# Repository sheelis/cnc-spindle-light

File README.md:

# Circular LED strip PCB for CNC spindle light

This is a PCB and spindle attachment design and software to light up the CNC work area from all sides in any color or sequence desired (as long as you can program it to). The LED control is done by FastLED library, so it's not too hard to create your own sequences.

There is also an option to insert 2 lasers at 90* difference from each other in order to produce a cross shape on XY plane exactly where the tool will touch the work piece. Lasers have their own connectors and on/off switch on the PCB.
There is also a provision for attaching the the Z probe to the pcb, but it is only tested on my own DIY CNC.

You will find here:
- Firmware for ATTiny85
- PCB design
- Spindle mount design

## Final result

Then milled the wooden mount and attached the LED ring and lasers. I did not insert the lasers fully because later i will need to rotate them to align with center.

The mounting holes on the PCB align with any 20mm increment profiles such as my 2080 C-beam

PCB milled with a 0.2mm HSS bit

And the assembled PCB

## Parts list

This project requires:
- 1x WS2812B LED strip (circular, 24 LEDs)
- 1x ATTiny85
- 2x line or cross lasers
- 1x button and 1x switch
- some 2.54mm headers and sockets
- 2x THT resistors (10K)
- 1x single-sided copper board
- wooden block for milling the mount from
- 1x arduino uno (only for programming the ATTiny85)

## Usage

1. Mill or 3D print the mount.
2. Mill or etch the PCB at home or get it done by a PCB factory.
3. Upload the firmware to ATTiny85 using your preferred method. I used an arduino UNO as ISP.
4. Solder on all the components (I suggest starting with the smallest ones)
5. Connect the 5v power and LED strip to PCB
6. Press the button to change the LED mode

PM me for questions and comments!

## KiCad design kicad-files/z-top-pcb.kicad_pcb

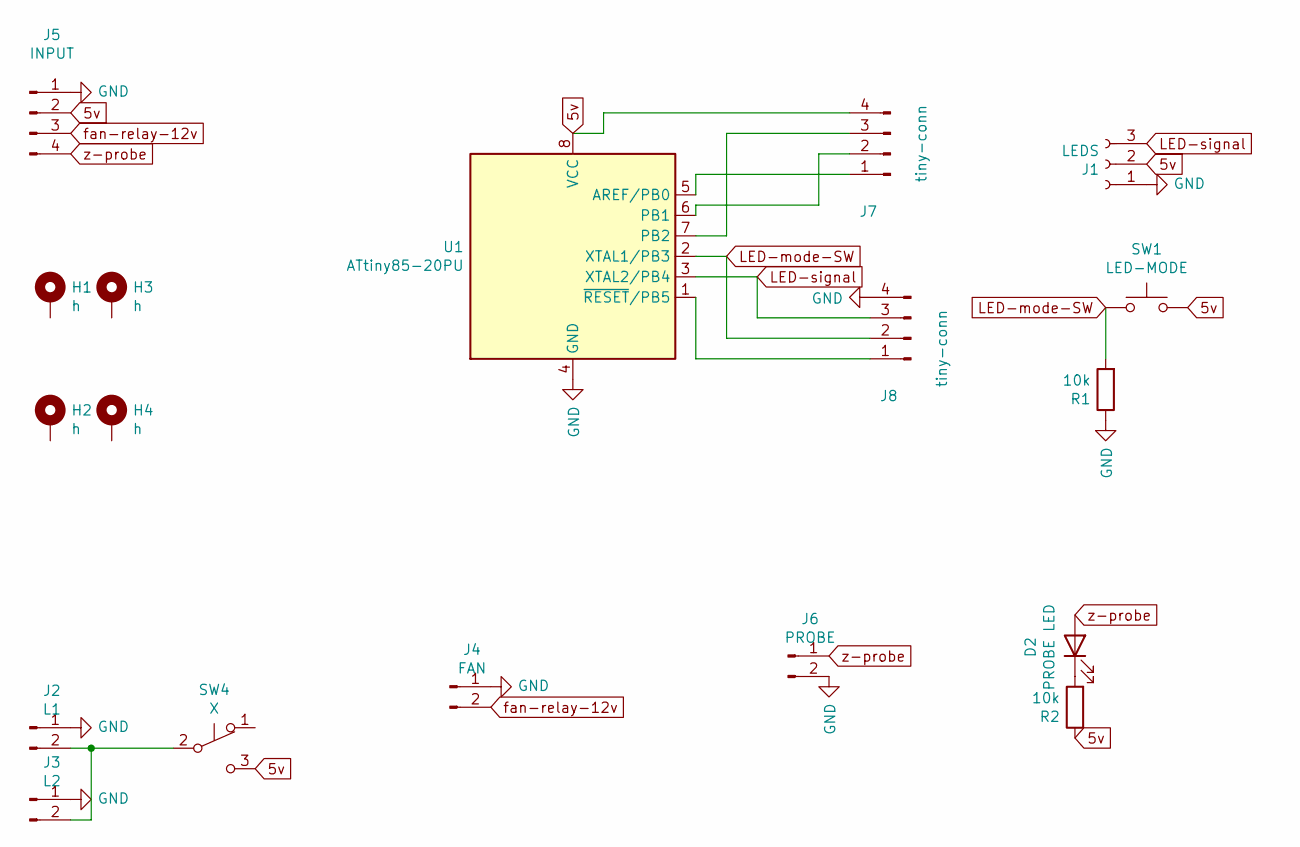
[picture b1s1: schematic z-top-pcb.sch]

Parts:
D2: PROBE LED; LED_D5.0mm_Clear
H1, H2, H3, H4: h; MountingHole_5.3mm_M5_ISO14580_Pad
J1: LEDS; PinSocket_1x03_P2.54mm_Vertical
J2: L1; PinSocket_1x02_P2.54mm_Vertical
J3: L2; PinSocket_1x02_P2.54mm_Vertical
J4: FAN; PinSocket_1x02_P2.54mm_Vertical
J5: INPUT; PinSocket_1x04_P2.54mm_Vertical
J6: PROBE; PinSocket_1x02_P2.54mm_Vertical
J7, J8: tiny-conn; PinHeader_1x04_P2.54mm_Vertical
R1, R2: 10k; R_Axial_DIN0207_L6.3mm_D2.5mm_P10.16mm_Horizontal
SW1: LED-MODE; SW_PUSH_6mm
SW4: X; SW_Slide_1P2T_CK_OS102011MS2Q
U1: ATtiny85-20PU; DIP-8_W7.62mm

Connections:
5v: J1.2, J5.2, J7.4, R2.1, SW1.2, SW4.3 (C), U1.8 (VCC)
GND: J1.1, J2.1, J3.1, J4.1, J5.1, J6.2, J8.4, R1.1, U1.4 (GND)
LED-mode-SW: J8.2, R1.2, SW1.1, U1.2 (XTAL1/PB3)
LED-signal: J1.3, J8.3, U1.3 (XTAL2/PB4)
unnamed: D2.1 (K), R2.2
unnamed: J2.2, J3.2, SW4.2 (B)
unnamed: J7.1, U1.5 (AREF/PB0)
unnamed: J7.2, U1.6 (PB1)
unnamed: J7.3, U1.7 (PB2)
unnamed: J8.1, U1.1 (~RESET~/PB5)
fan-relay-12v: J4.2, J5.3
z-probe: D2.2 (A), J5.4, J6.1

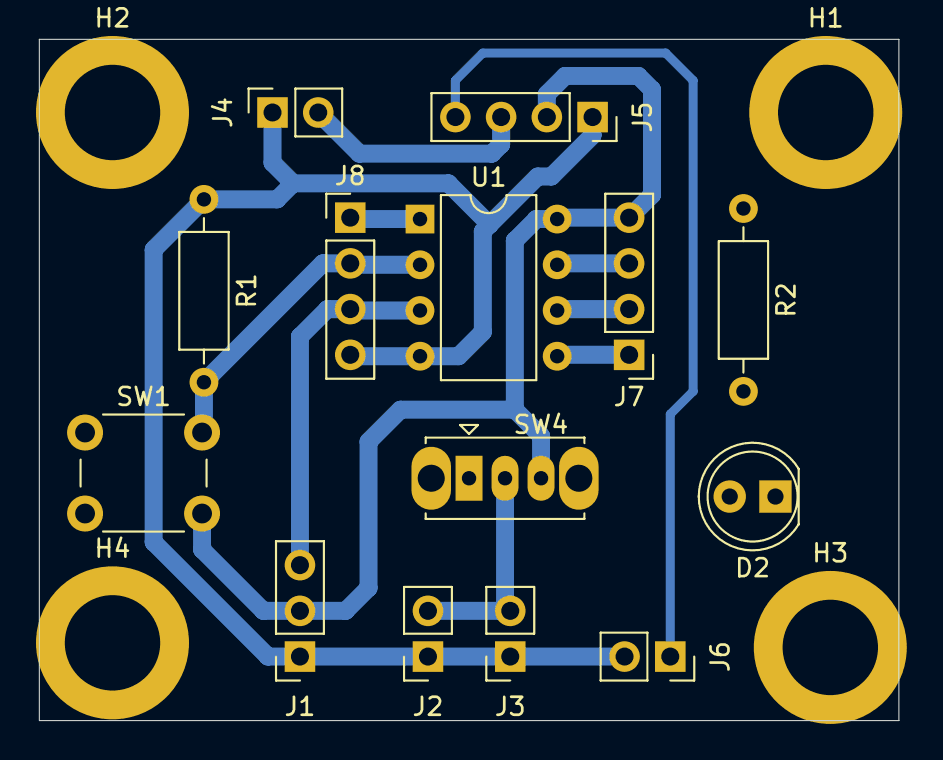
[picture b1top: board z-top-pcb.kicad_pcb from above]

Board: 2 copper layers, 47.8 x 37.8 mm, 18 parts (0 on the bottom side), 12 nets.

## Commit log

2021-04-14 added gitignore, description
2021-04-14 Parts list and usage
2021-04-14 added images and 3d files
2021-04-15 images and mount model
2021-04-15 mount images
2021-04-15 about lasers...
2021-04-15 more on parts and PCB
2021-04-15 about LEDs
2021-04-15 parts list
2021-06-23 added images and descriptions
